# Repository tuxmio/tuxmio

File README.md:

## Hi there 👋
This project was started to combine industrial controllers, open-source controllers, and the freedom of customization.

1. Project Name & Description
   
    TUXMIO= 2XMIO=MIO+MIO=Make It Own Modular Input/Output System
TUXMIO is a customizable Modular Input/Output System. It allows users to mix and match hardware while keeping full control over their automation systems.

2. Features
   
    ✔ Modular Design – Easily expand and customize I/O modules based on project needs.
  
    ✔ Hybrid Compatibility – Works with both industrial controllers (PLC, DCS) and open-source hardware (Arduino, ESP32, Raspberry Pi).
  
    ✔ Cross-Platform Support – Works with Linux, Windows, and embedded systems.
  
    ✔ Industrial-Grade Reliability – Designed for rugged environments with robust protection features.
  
    ✔ Flexible Manufacturing Options – Users can build it themselves, order custom production, or buy pre-assembled modules.

3. Installation & Setup
   
    Hardware:
  
    ✔ Choose your favorite open-source controller
  
    ✔ Connect it to TUXMIO
  
    ✔ Enjoy your controller in an industrial environment
  
    Software & Setup:
  
    Use your usual tools for firmware installation, configuration, and testing—just like you always do!

4. Usage

    After setup, just start your system and enjoy your creation.

5. Hardware Requirements

    ✔ Choose your favorite open-source controller (Arduino, Raspberry Pi, ESP32, etc.).
   
    ✔ TUXMIO modules (customize based on your needs).
   
    ✔ You can prepare your own power supply voltages, or use the TUXMIO PS board for convenience.
   
    ✔ Any additional sensors, actuators, or peripherals based on your project.

6. Contributing

    Hey, I’m not a professional in electronics, 3D design, or prototyping, so please be understanding and forgiving if you spot any mistakes or discrepancies. 😊
   
    If you’d like to help out, here’s how you can contribute:
   
      ✔ Fork the Repo: Feel free to fork this repo and create a branch with your changes.
   
      ✔ Submit a Pull Request: When you're ready, send over a pull request!
   
      ✔ Report Issues: If you notice any bugs or have suggestions, don’t hesitate to open an issue.
   
      ✔ Join the Fun: Let’s work together to make this project better and take it to new heights!

7. License
   TUXMIO is proudly open in both mind and design.
All software and firmware are shared under the MIT License — free to use, modify, and remix however you like.
All hardware designs (schematics, PCBs, 3D models) follow the CERN Open Hardware License – Permissive v2.0, allowing you to build, improve, and even sell your own versions, as long as you keep the original attribution intact! 😊

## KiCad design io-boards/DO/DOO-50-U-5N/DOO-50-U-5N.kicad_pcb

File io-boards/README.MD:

┌──────┬────────────┬───────────┬─────────────────────────────────────────────┬───────────────────────────────────────────────────────────────────────────────┐
│ Code │ Complexity │ Priority  │ Description                                 │ Notes                                                                         │
├──────┼────────────┼───────────┼─────────────────────────────────────────────┼───────────────────────────────────────────────────────────────────────────────┤
│ DI   │ 0          │ 1         │ Direct digital input (NPN/PNP stabilized)   │ Simple design, direct to MCU or buffer input.                                 │
│ DI   │ 4          │ -         │ Differential digital input (super-fast OC)  │ High-speed differential inputs, open-collector tolerant.                      │
│ DI   │ 2          │ -         │ Optocoupled digital input (NPN/PNP)         │ Isolated voltage sensing, moderate complexity.                                │
│ DO   │ 0          │ 1         │ Direct digital output (NPN/PNP stabilized)  │ Transistor-based output, low-side/high-side variants possible.                │
│ DO   │ 2          │ -         │ Optocoupled digital output (short-prot.)    │ Protected, diagnostic LEDs, block on short.                                   │
│ DO   │ 4          │ -         │ Super-fast optocoupled digital output       │ High-speed driver, isolation + diagnostics.                                   │
│ DO   │ 4          │ -         │ Differential digital output (OC)            │ Fast differential output, open-collector style.                               │
│ DO   │ 1          │ 2         │ Relay output                                │ Mechanical relay, user-changeable type.                                       │
│ DO   │ 1          │ 2         │ SSR relay output                            │ Solid State Relay variant.                                                    │
│ AI   │ 0          │ 1         │ Direct analog input 0–5V                    │ Basic ADC interface.                                                          │
│ AI   │ 1          │ -         │ 0–10V analog input                          │ Most common industrial input range.                                           │
│ AI   │ 2          │ -         │ ±10V analog input                           │ Bipolar measurement range.                                                    │
│ AI   │ 4          │ 5         │ 0–5mA analog input                          │ Requires precise current sensing, maybe external supply.                      │
│ AI   │ 4          │ 5         │ 0–20mA analog input                         │ Current loop sensing, possibly needs shunt resistor.                          │
│ AI   │ 4          │ 5         │ Low-voltage 0–10mV analog input             │ For small-signal sensors, instrumentation amp required.                       │
│ AI   │ 3          │ 5         │ Thermocouple input                          │ Requires CJC, precision ADC, low noise.                                       │
│ AI   │ 3          │ 5         │ RTD input (PT100/PT1000)                    │ Requires excitation and bridge measurement.                                   │
│ AO   │ 0          │ 1         │ Direct analog output 0–5V                   │ Simple DAC output.                                                            │
│ AO   │ 2          │ 2         │ 0–10V analog output                         │ Standard industrial output range.                                             │
│ AO   │ 2          │ 5         │ ±10V analog output                          │ Bipolar DAC driver, requires dual supply.                                     │
│ AO   │ 4          │ 3         │ 0–20mA analog output                        │ Current loop output, supply-dependent.                                        │
└──────┴────────────┴───────────┴─────────────────────────────────────────────┴───────────────────────────────────────────────────────────────────────────────┘

Enhanced I/O Function Table with ABC Codes
#	Old Code	New Code	Description	Notes / Feature keywords
1	DI	DID	Direct Digital Input (NPN/PNP stabilized)	simplest form, direct connection
2	DI	DIF	Differential Digital Input (superfast OC)	high-speed, open-collector compatible
3	DI	DIO	Optocoupled Digital Input (NPN/PNP voltage)	isolated, standard industrial input
4	DO	DOD	Direct Digital Output (NPN/PNP stabilized)	simple transistor output
5	DO	DOO	Optocoupled Digital Output (short-prot, diag)	isolated, protected, LED indicators
6	DO	DOF	Fast Optocoupled Digital Output (superfast)	high-speed variant
7	DO	DOH	Differential (High-speed OC) Digital Output	OC differential drivers
8	DO	DOR	Relay Output (mechanical relays)	changeable relay sockets
9	DO	DOS	SSR Output (Solid-State Relay)	solid-state version
10	AI	AIV	Analog Voltage Input (0–5V, 0–10V, ±10V)	voltage-based measurement
11	AI	AIC	Analog Current Input (0–5mA, 0–20mA)	current loop or shunt measurement
12	AI	AIL	Low-Voltage / Millivolt Input	instrumentation, low-noise sensors
13	AI	AIT	Thermocouple Input	temperature, requires CJC
14	AI	AIR	Resistance / RTD Input (PT100/PT1000)	with excitation and linearization
15	AO	AOV	Analog Voltage Output (0–5V, 0–10V, ±10V)	DAC-based voltage output
16	AO	AOC	Analog Current Output (0–20mA)	current loop output
17	COM	CCI	Communication Interface Input (e.g., RS, CAN)	receives data
18	COM	CCO	Communication Interface Output	transmits data
19	COM	CCX	Communication Transceiver / Bidirectional	bidirectional (e.g., RS485, CAN, I²C)

1st letter: Domain
D → Digital
A → Analog
C → Communication

2nd letter: Direction
I → Input
O → Output
X → Bidirectional / mixed

3rd letter: Feature

D = Direct
O = Optocoupled
F = Fast / Differential
R = Relay
S = Solid State
V = Voltage
C = Current
L = Low voltage / millivolt
T = Thermocouple
R = RTD (resistance sensor)
H = High-speed / OC
X = Mixed / special

┌────────────┬───────────┬───────────────────────────────────────────────┐
│ Letter Pos │ Represents│ Example Letters / Meaning                     │
├────────────┼───────────┼───────────────────────────────────────────────┤
│ 1st        │ Domain    │ D = Digital, A = Analog, C = Communication    │
│ 2nd        │ Direction │ I = Input, O = Output, X = Bidirectional      │
│ 3rd        │ Feature   │ D = Direct, O = Optocoupled, F = Fast,        │
│            │           │ R = Relay, S = Solid-state, V = Voltage,      │
│            │           │ C = Current, L = Low-voltage, T = TC, R = RTD │
└────────────┴───────────┴───────────────────────────────────────────────┘

<ABC>-<LS>-<PT>-<RPO>-Vx.xx

where:
ABC = 3-letter functional code = [Domain][Direction][Feature]
    Domain: A = Analog, D = Digital (use “Digital”), C = Communication
    Direction: I = Input, O = Output, X = Bidirectional
    Feature: domain-specific (e.g. D=Direct, O=Optocoupled, F=Fast/Differential, R=Relay, S=SolidState, V=Voltage, C=Current, L=Low-voltage, T=Thermocouple, R=RTD, H=High-speed, X=Mixed)
LS = two digits: [LogicLevel][SocketType]
    LogicLevel (first digit): 3 = 3.3 V logic, 5 = 5 V logic, 9 = Mixed/Auto/Dual
    SocketType (second digit): 0 = Socket A, 1 = Socket B, 2 = Socket C, 3 = Socket D
PT = Peripheral Type (single letter)
    U = Voltage-type peripheral
    C = Current-type peripheral
RPO = Range code + Peripheral Option (two chars)
Range code (digit): Voltage codes (for U)
    0 = sink-mode NPN (logic sink)
    1 = 3.3/5 V logic-level field
    2 = 10 V
    3 = 12 V
    4 = 15 V
    5 = 24 V
    6 = 230 VAC
Range code (digit): Current codes (for C)
    0 = 0–5 mA
    1 = 0–20 mA
    2 = 4–20 mA
    3 = −20 mA … +20 mA
Peripheral Option (letter, immediately after range digit):
    N = Sink mode (NPN)
    P = Source mode (PNP)
    B = Bipolar
Vx.xx = Version (major.minor) e.g. V0.01

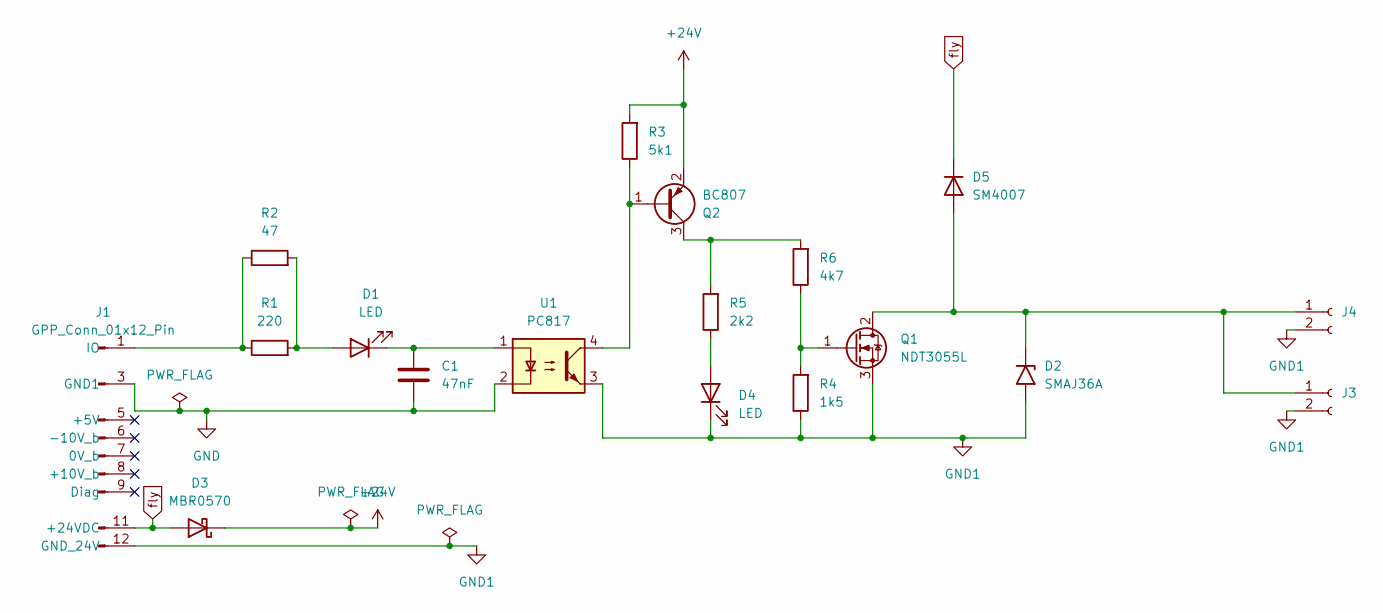
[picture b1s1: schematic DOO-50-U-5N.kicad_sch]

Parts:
C1: 47nF; C_0201_0603Metric
D1, D4: LED; LED_0402_1005Metric_Pad0.77x0.64mm_HandSolder
D2: SMAJ36A; D_SMA
D3: MBR0570; D_SOD-123
D5: SM4007; D_MELF_Handsoldering
J1: GPP_Conn_01x12_Pin; IO_GPP_PinHeader_1x12_P2.54mm_Horizontal
J3: Conn_01x02_Socket; KF141x_SMD
J4: Conn_01x02_Socket; PinSocket_1x02_P2.54mm_Horizontal
Q1: NDT3055L; SOT-223-3_TabPin2
Q2: BC807; SOT-23
R1: 220; R_0402_1005Metric_Pad0.72x0.64mm_HandSolder
R2: 47; R_0402_1005Metric_Pad0.72x0.64mm_HandSolder
R3: 5k1; R_0402_1005Metric_Pad0.72x0.64mm_HandSolder
R4: 1k5; R_0402_1005Metric_Pad0.72x0.64mm_HandSolder
R5: 2k2; R_0402_1005Metric_Pad0.72x0.64mm_HandSolder
R6: 4k7; R_0402_1005Metric_Pad0.72x0.64mm_HandSolder
U1: PC817; DIP-4_W7.62mm_SMDSocket_SmallPads

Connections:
+24V: D3.1 (K), Q2.2 (E), R3.2
GND: C1.2, J1.3 (GND1), U1.2
GND1: D2.2 (A2), D4.1 (K), J1.12 (GND_24V), J3.2, J4.2, Q1.3 (S), R4.1, U1.3
unnamed: D1.2 (A), R1.2, R2.2
unnamed: C1.1, D1.1 (K), U1.1
unnamed: D2.1 (A1), D5.2 (A), J3.1, J4.1, Q1.2 (D)
unnamed: D4.2 (A), R5.1
unnamed: J1.1 (IO), R1.1, R2.1
unnamed: Q1.1 (G), R4.2, R6.1
unnamed: Q2.1 (B), R3.1, U1.4
unnamed: Q2.3 (C), R5.2, R6.2
fly: D3.2 (A), D5.1 (K), J1.11 (+24VDC)

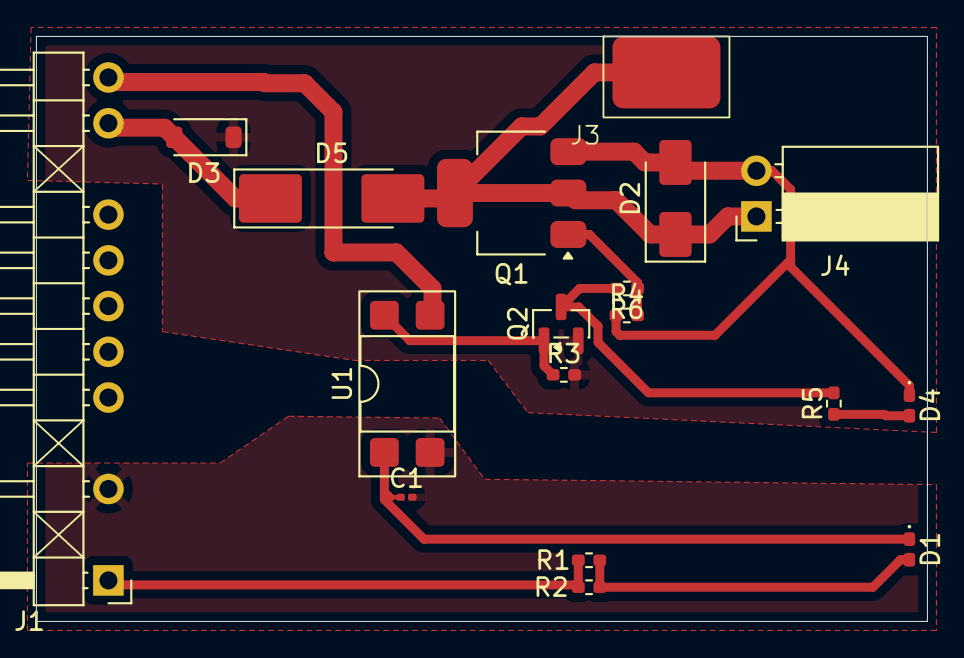
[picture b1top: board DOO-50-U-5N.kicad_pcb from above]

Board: 2 copper layers, 49.5 x 32.5 mm, 18 parts (0 on the bottom side), 12 nets.

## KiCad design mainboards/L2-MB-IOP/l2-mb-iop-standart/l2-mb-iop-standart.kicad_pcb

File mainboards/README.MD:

TUXMIO Mainboard Classification
┌──────────────┬──────────────────────────────┬────────┬──────────────────────────────────────────────────────────────────────────────┐
│ Directory    │ Full Name                    │ Level  │ Description                                                                  │
├──────────────┼──────────────────────────────┼────────┼──────────────────────────────────────────────────────────────────────────────┤
│ L0-MB-PML    │ Power Management Layer       │ L0     │ Handles power entry, conversion, and protection (fuse, surge, polarity).     │
│              │                              │        │ Supplies regulated voltages to upper layers.                                 │
├──────────────┼──────────────────────────────┼────────┼──────────────────────────────────────────────────────────────────────────────┤
│ L1-MB-CIM    │ Controller Interface Module  │ L1     │ Hosts the main controller (MCU, SBC, or SoM). Manages logic, communication   │
│              │                              │        │ and links between the power and I/O layers.                                  │
├──────────────┼──────────────────────────────┼────────┼──────────────────────────────────────────────────────────────────────────────┤
│ L2-MB-IOP    │ Input/Output Peripherals     │ L2     │ Provides interface for I/O boards, sensors, and actuators. Includes sockets  │
│              │                              │        │ for I/O boards. each socket only supports specific I/O board types           │
└──────────────┴──────────────────────────────┴────────┴──────────────────────────────────────────────────────────────────────────────┘
 
   ┌┐   ┌┐   ┌┐   ┌┐   ┌┐   ┌┐   ┌┐   
   ||   ||   ||   ||   ||   ||   ||
   ||   ||   ||   ||   ||   ||   ||  ← I/O Boards
   ||   ||   ||   ||   ||   ||   ||
   └┘   └┘   └┘   └┘   └┘   └┘   └┘   
   ┌──────────────────────────────┐
   │  L2 – MB-IOP  (Peripherals)  │  ← I/O Expansion Layer
   └─────────────┬────────────────┘
                 │
   ┌─────────────┴────────────────┐
   │  L1 – MB-CIM  (Controller)   │  ← Processing & Communication Layer
   └─────────────┬────────────────┘
                 │
   ┌─────────────┴────────────────┐
   │  L0 – MB-PML  (Power)        │  ← Power & Protection Base Layer
   └──────────────────────────────┘

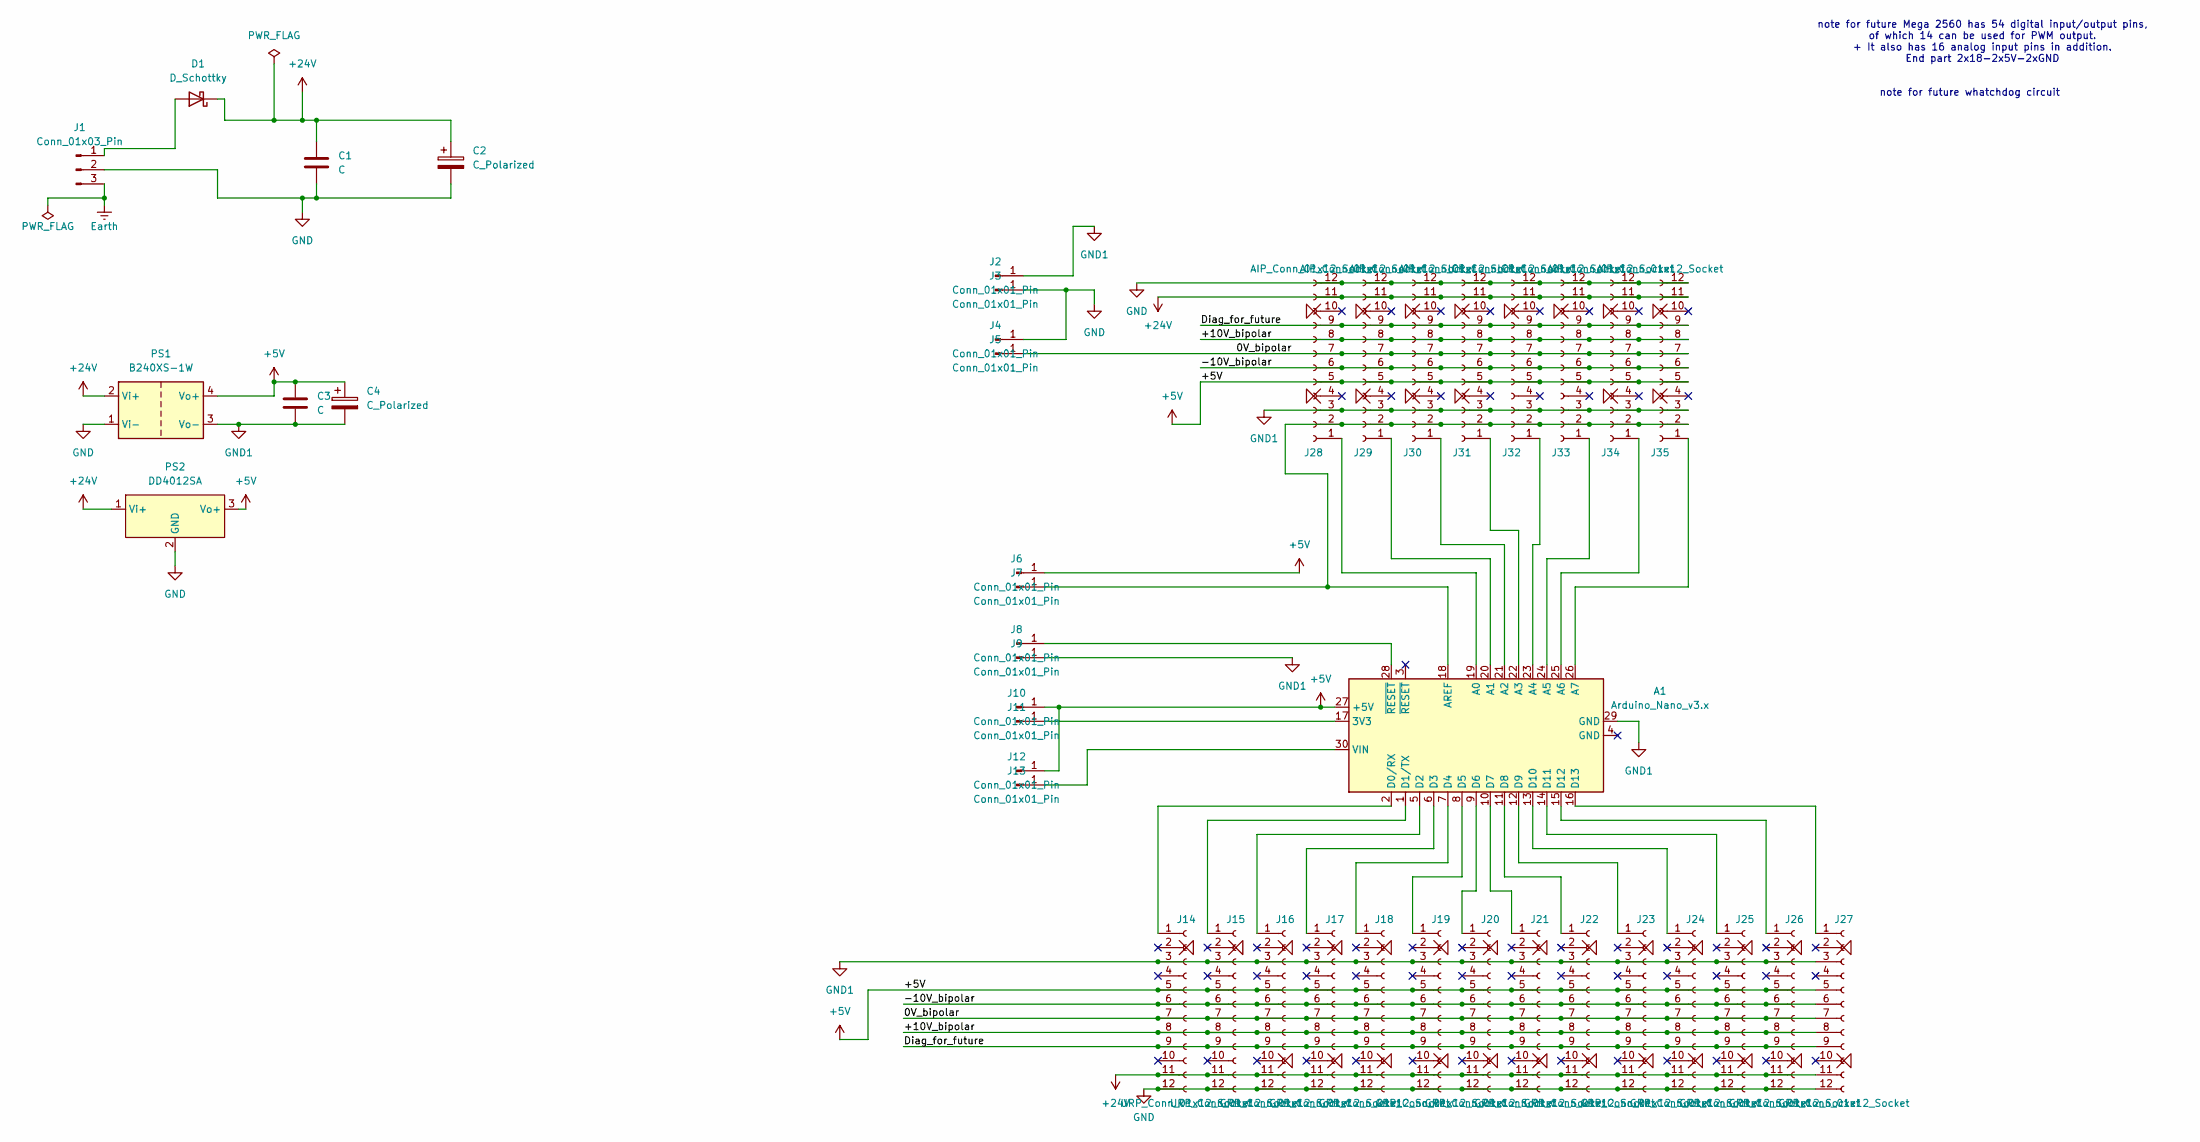
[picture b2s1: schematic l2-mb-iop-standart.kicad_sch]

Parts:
A1: Arduino_Nano_v3.x; Arduino_Nano
C1, C3: C
C2, C4: C_Polarized
D1: D_Schottky
J1: Conn_01x03_Pin
J2, J3, J4, J5, J6, J7, J8, J9, J10, J11, J12, J13: Conn_01x01_Pin
J14, J15: URP_Conn_01x12_Socket; MB_URP_PinSocket_1x12_P2.54mm_Vertical
J16, J17, J18, J19, J20, J21, J22, J23, J24, J25, J26, J27: GPP_Conn_01x12_Socket; MB_GPP_PinSocket_1x12_P2.54mm_Vertical
J28, J29, J30, J31, J34, J35: AIP_Conn_01x12_Socket; MB_AIP_PinSocket_1x12_P2.54mm_Vertical
J32, J33: ICP_Conn_01x12_Socket; MB_ICP_PinSocket_1x12_P2.54mm_Vertical
PS1: B240XS-1W
PS2: DD4012SA

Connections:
+5V: A1.27 (+5V), C3.1, C4.1, J6.1, J10.1, J12.1, J14.5 (Diag), J15.5 (Diag), J16.5 (Diag), J17.5 (Diag), J18.5 (Diag), J19.5 (Diag), J20.5 (Diag), J21.5 (Diag), J22.5 (Diag), J23.5 (Diag), J24.5 (Diag), J25.5 (Diag), J26.5 (Diag), J27.5 (Diag), J28.5 (Diag), J29.5 (Diag), J30.5 (Diag), J31.5 (Diag), J32.5 (Diag), J33.5 (Diag), J34.5 (Diag), J35.5 (Diag), PS1.4 (Vo+), PS2.3 (Vo+)
+24V: C1.1, C2.1, D1.1 (K), J14.11 (+24VDC), J15.11 (+24VDC), J16.11 (+24VDC), J17.11 (+24VDC), J18.11 (+24VDC), J19.11 (+24VDC), J20.11 (+24VDC), J21.11 (+24VDC), J22.11 (+24VDC), J23.11 (+24VDC), J24.11 (+24VDC), J25.11 (+24VDC), J26.11 (+24VDC), J27.11 (+24VDC), J28.11 (+24VDC), J29.11 (+24VDC), J30.11 (+24VDC), J31.11 (+24VDC), J32.11 (+24VDC), J33.11 (+24VDC), J34.11 (+24VDC), J35.11 (+24VDC), PS1.2 (Vi+), PS2.1 (Vi+)
/0V_bipolar: J5.1, J14.7 (0V_b), J15.7 (0V_b), J16.7 (0V_b), J17.7 (0V_b), J18.7 (0V_b), J19.7 (0V_b), J20.7 (0V_b), J21.7 (0V_b), J22.7 (0V_b), J23.7 (0V_b), J24.7 (0V_b), J25.7 (0V_b), J26.7 (0V_b), J27.7 (0V_b), J28.7 (0V_b), J29.7 (0V_b), J30.7 (0V_b), J31.7 (0V_b), J32.7 (0V_b), J33.7 (0V_b), J34.7 (0V_b), J35.7 (0V_b)
/+10V_bipolar: J14.8 (+10V_b), J15.8 (+10V_b), J16.8 (+10V_b), J17.8 (+10V_b), J18.8 (+10V_b), J19.8 (+10V_b), J20.8 (+10V_b), J21.8 (+10V_b), J22.8 (+10V_b), J23.8 (+10V_b), J24.8 (+10V_b), J25.8 (+10V_b), J26.8 (+10V_b), J27.8 (+10V_b), J28.8 (+10V_b), J29.8 (+10V_b), J30.8 (+10V_b), J31.8 (+10V_b), J32.8 (+10V_b), J33.8 (+10V_b), J34.8 (+10V_b), J35.8 (+10V_b)
/-10V_bipolar: J14.6 (-10V_b), J15.6 (-10V_b), J16.6 (-10V_b), J17.6 (-10V_b), J18.6 (-10V_b), J19.6 (-10V_b), J20.6 (-10V_b), J21.6 (-10V_b), J22.6 (-10V_b), J23.6 (-10V_b), J24.6 (-10V_b), J25.6 (-10V_b), J26.6 (-10V_b), J27.6 (-10V_b), J28.6 (-10V_b), J29.6 (-10V_b), J30.6 (-10V_b), J31.6 (-10V_b), J32.6 (-10V_b), J33.6 (-10V_b), J34.6 (-10V_b), J35.6 (-10V_b)
/Diag_for_future: J14.9 (N/A_Pin_9), J15.9 (N/A_Pin_9), J16.9 (N/A_Pin_9), J17.9 (N/A_Pin_9), J18.9 (N/A_Pin_9), J19.9 (N/A_Pin_9), J20.9 (N/A_Pin_9), J21.9 (N/A_Pin_9), J22.9 (N/A_Pin_9), J23.9 (N/A_Pin_9), J24.9 (N/A_Pin_9), J25.9 (N/A_Pin_9), J26.9 (N/A_Pin_9), J27.9 (N/A_Pin_9), J28.9 (N/A_Pin_9), J29.9 (N/A_Pin_9), J30.9 (N/A_Pin_9), J31.9 (N/A_Pin_9), J32.9 (N/A_Pin_9), J33.9 (N/A_Pin_9), J34.9 (N/A_Pin_9), J35.9 (N/A_Pin_9)
Earth: J1.3
GND: C1.2, C2.2, J1.2, J3.1, J4.1, J14.12 (GND_24V), J15.12 (GND_24V), J16.12 (GND_24V), J17.12 (GND_24V), J18.12 (GND_24V), J19.12 (GND_24V), J20.12 (GND_24V), J21.12 (GND_24V), J22.12 (GND_24V), J23.12 (GND_24V), J24.12 (GND_24V), J25.12 (GND_24V), J26.12 (GND_24V), J27.12 (GND_24V), J28.12 (GND_24V), J29.12 (GND_24V), J30.12 (GND_24V), J31.12 (GND_24V), J32.12 (GND_24V), J33.12 (GND_24V), J34.12 (GND_24V), J35.12 (GND_24V), PS1.1 (Vi-), PS2.2 (GND)
GND1: A1.29 (GND), C3.2, C4.2, J2.1, J9.1, J14.3 (GND1), J15.3 (GND1), J16.3 (GND1), J17.3 (GND1), J18.3 (GND1), J19.3 (GND1), J20.3 (GND1), J21.3 (GND1), J22.3 (GND1), J23.3 (GND1), J24.3 (GND1), J25.3 (GND1), J26.3 (GND1), J27.3 (GND1), J28.3 (GND1), J29.3 (GND1), J30.3 (GND1), J31.3 (GND1), J32.3 (GND1), J33.3 (GND1), J34.3 (GND1), J35.3 (GND1), PS1.3 (Vo-)
unnamed: A1.17 (3V3), J11.1
unnamed: A1.19 (A0), J28.1 (IO)
unnamed: A1.20 (A1), J29.1 (IO)
unnamed: A1.21 (A2), J30.1 (IO)
unnamed: A1.22 (A3), J31.1 (IO)
unnamed: A1.23 (A4), J32.1 (IO)
unnamed: A1.24 (A5), J33.1 (IO)
unnamed: A1.25 (A6), J34.1 (IO)
unnamed: A1.26 (A7), J35.1 (IO)
unnamed: A1.18 (AREF), J7.1, J28.2 (A_Ref), J29.2 (A_Ref), J30.2 (A_Ref), J31.2 (A_Ref), J32.2 (A_Ref), J33.2 (A_Ref), J34.2 (A_Ref), J35.2 (A_Ref)
unnamed: A1.2 (D0/RX), J14.1 (IO)
unnamed: A1.1 (D1/TX), J15.1 (IO)
unnamed: A1.5 (D2), J16.1 (IO)
unnamed: A1.6 (D3), J17.1 (IO)
unnamed: A1.7 (D4), J18.1 (IO)
unnamed: A1.8 (D5), J19.1 (IO)
unnamed: A1.9 (D6), J20.1 (IO)
unnamed: A1.10 (D7), J21.1 (IO)
unnamed: A1.11 (D8), J22.1 (IO)
unnamed: A1.12 (D9), J23.1 (IO)
unnamed: A1.13 (D10), J24.1 (IO)
unnamed: A1.14 (D11), J25.1 (IO)
unnamed: A1.15 (D12), J26.1 (IO)
unnamed: A1.16 (D13), J27.1 (IO)
unnamed: A1.30 (VIN), J13.1
unnamed: D1.2 (A), J1.1
unnamed: A1.28 (~RESET), J8.1

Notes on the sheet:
note for future Mega 2560 has 54 digital input/output pins, of which 14 can be used for PWM output. + It also has 16 analog input pins in addition. End part 2x18-2x5V-2xGND
note for future whatchdog circuit

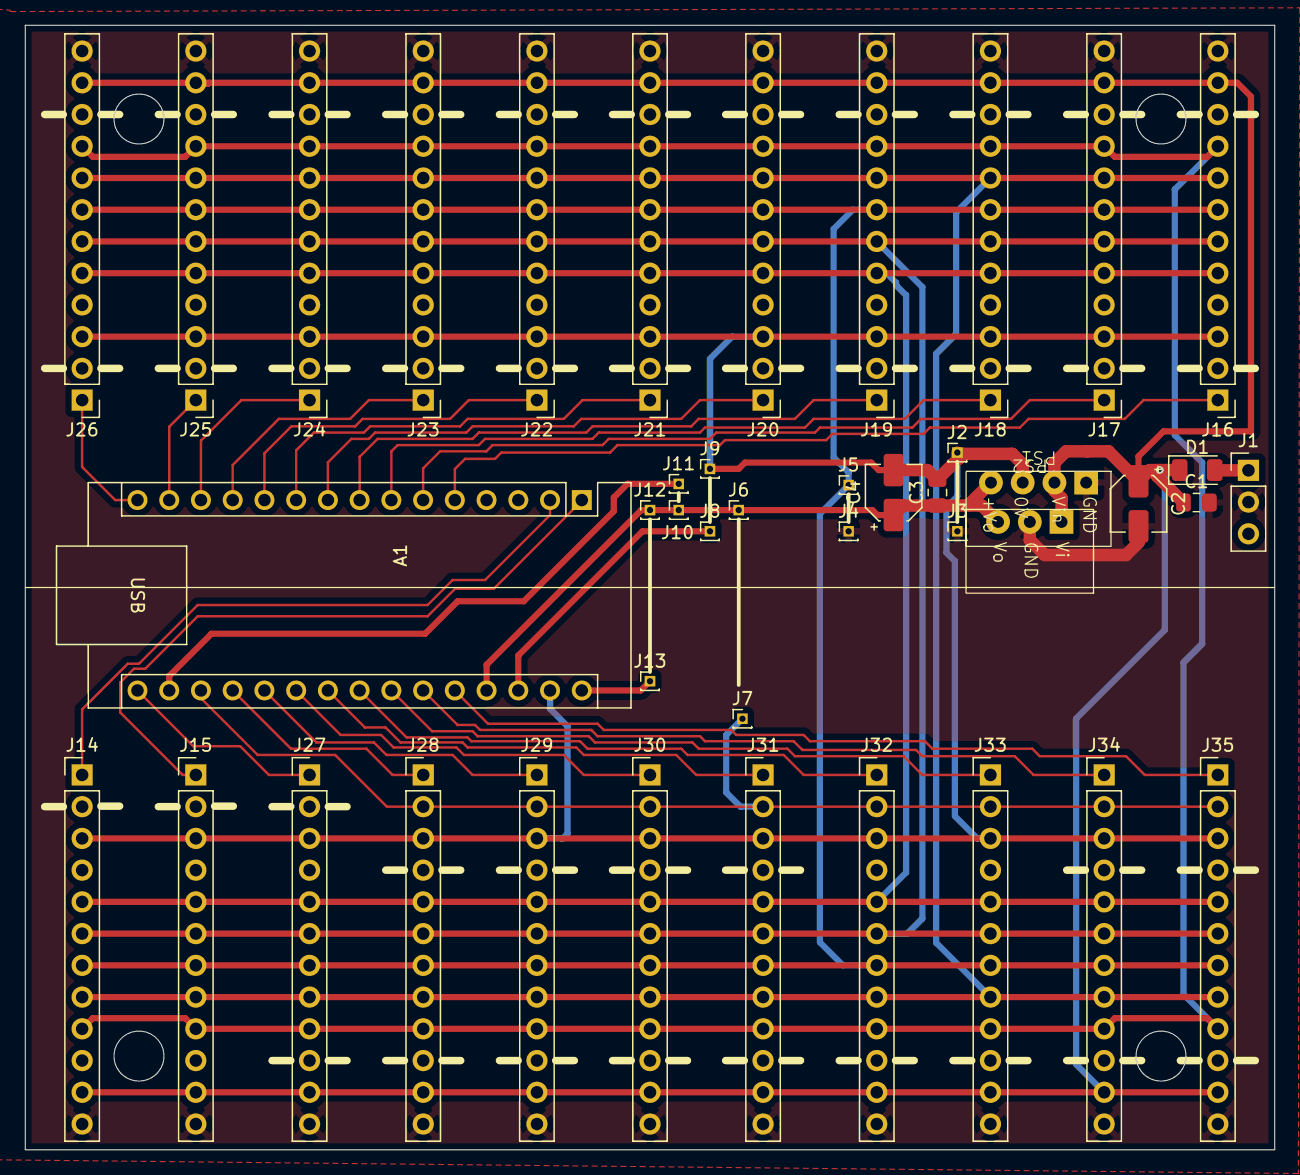
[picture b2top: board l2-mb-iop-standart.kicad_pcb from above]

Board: 2 copper layers, 100.0 x 90.0 mm, 43 parts (0 on the bottom side), 35 nets.

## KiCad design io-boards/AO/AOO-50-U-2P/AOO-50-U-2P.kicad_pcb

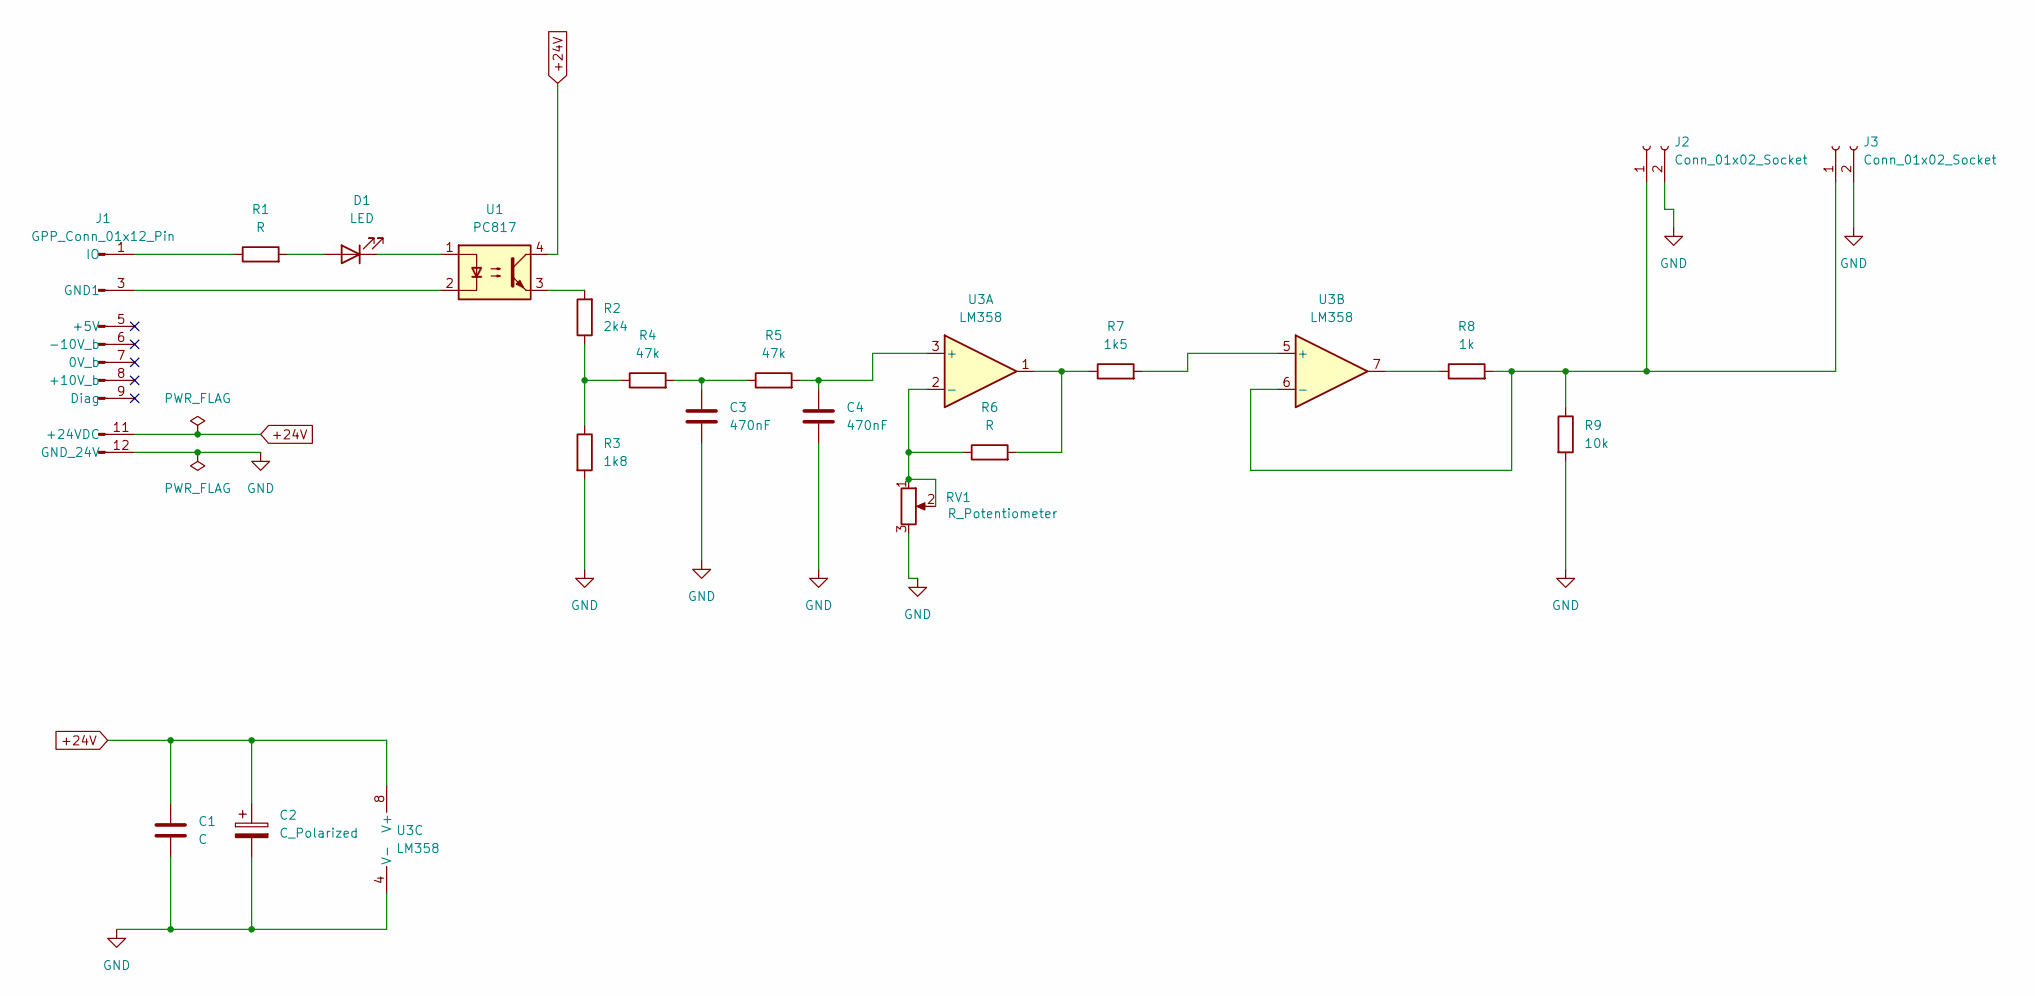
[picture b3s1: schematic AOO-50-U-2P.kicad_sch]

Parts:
C1: C; C_Disc_D4.7mm_W2.5mm_P5.00mm
C2: C_Polarized; CP_Radial_D4.0mm_P2.00mm
C3, C4: 470nF; C_Disc_D6.0mm_W2.5mm_P5.00mm
D1: LED; LED_D3.0mm
J1: GPP_Conn_01x12_Pin; IO_GPP_PinHeader_1x12_P2.54mm_Horizontal
J2: Conn_01x02_Socket; KF141x_SMD
J3: Conn_01x02_Socket; PinSocket_1x02_P2.54mm_Horizontal
R1, R6: R; R_Axial_DIN0204_L3.6mm_D1.6mm_P5.08mm_Horizontal
R2: 2k4; R_Axial_DIN0204_L3.6mm_D1.6mm_P5.08mm_Horizontal
R3: 1k8; R_Axial_DIN0204_L3.6mm_D1.6mm_P5.08mm_Horizontal
R4, R5: 47k; R_Axial_DIN0204_L3.6mm_D1.6mm_P5.08mm_Horizontal
R7: 1k5; R_Axial_DIN0204_L3.6mm_D1.6mm_P5.08mm_Horizontal
R8: 1k; R_Axial_DIN0204_L3.6mm_D1.6mm_P5.08mm_Horizontal
R9: 10k; R_Axial_DIN0204_L3.6mm_D1.6mm_P5.08mm_Horizontal
RV1: R_Potentiometer; Potentiometer_Vishay_148-149_Single_Vertical
U1: PC817; DIP-4_W7.62mm_SMDSocket_SmallPads
U3: LM358; DIP-8_W7.62mm

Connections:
+24V: C1.1, C2.1, J1.11 (+24VDC), U1.4, U3.8 (V+)
GND: C1.2, C2.2, C3.2, C4.2, J1.12 (GND_24V), J2.2, J3.2, R3.2, R9.2, RV1.3, U3.4 (V-)
unnamed: C3.1, R4.2, R5.1
unnamed: D1.2 (A), R1.2
unnamed: D1.1 (K), U1.1
unnamed: J1.3 (GND1), U1.2
unnamed: J1.1 (IO), R1.1
unnamed: J2.1, J3.1, R8.2, R9.1, U3.6 (-)
unnamed: R2.1, R3.1, R4.1
unnamed: R2.2, U1.3
unnamed: R6.2, R7.1, U3.1
unnamed: R8.1, U3.7
unnamed: C4.1, R5.2, U3.3 (+)
unnamed: R6.1, RV1.1, RV1.2, U3.2 (-)
unnamed: R7.2, U3.5 (+)

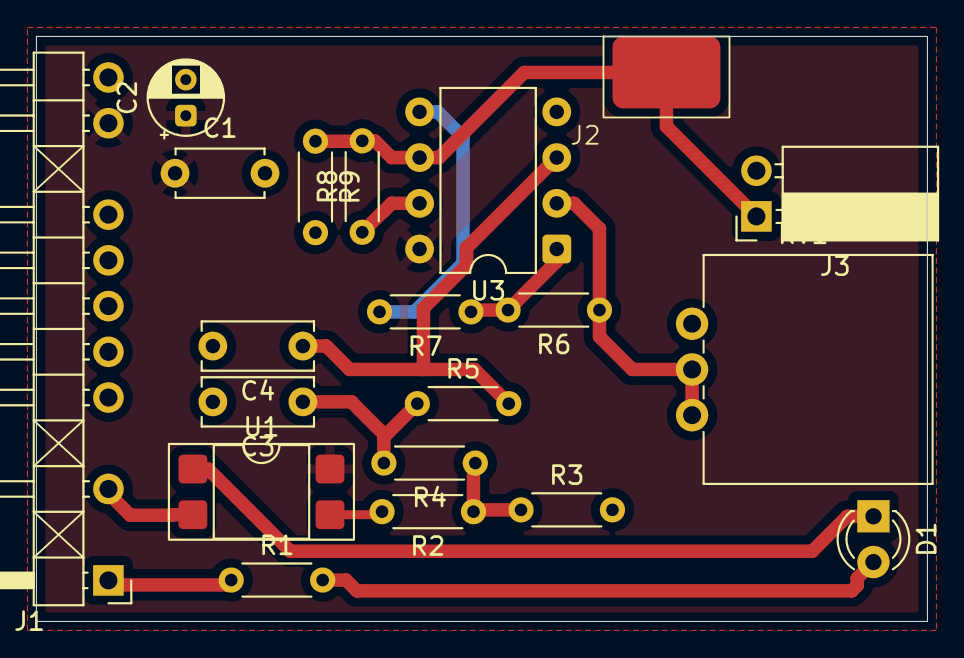
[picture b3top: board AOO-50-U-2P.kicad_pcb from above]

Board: 2 copper layers, 49.5 x 32.5 mm, 20 parts (0 on the bottom side), 15 nets.

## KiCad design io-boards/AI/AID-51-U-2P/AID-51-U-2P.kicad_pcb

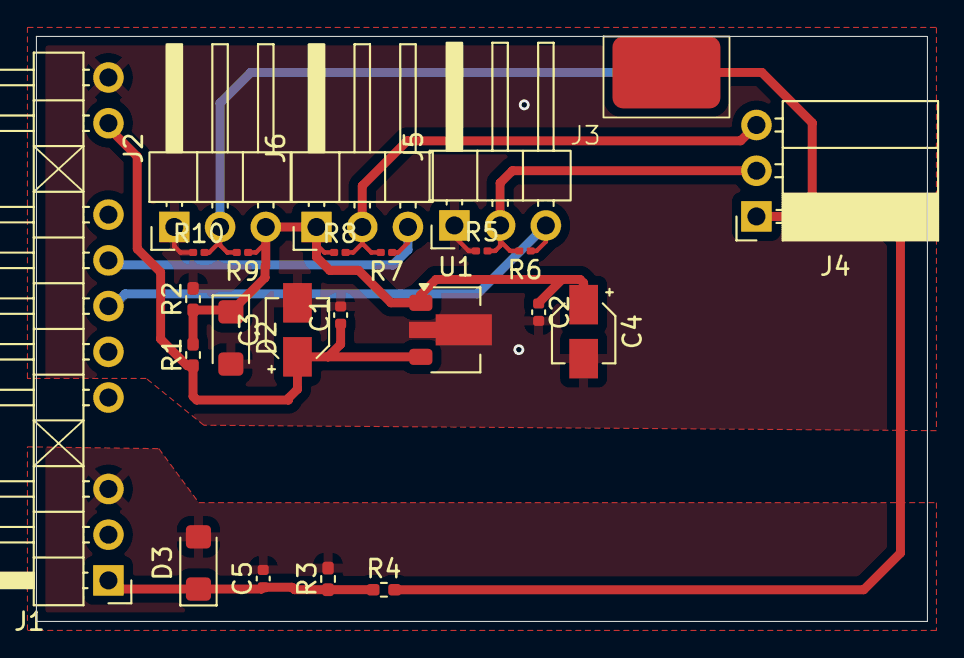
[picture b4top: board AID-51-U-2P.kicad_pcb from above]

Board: 2 copper layers, 49.5 x 32.5 mm, 24 parts (0 on the bottom side), 11 nets.

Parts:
C1, C2: 100nF; C_0402_1005Metric
C3: 10uf 50V; CP_Elec_3x5.3
C4: 10uF 50V; CP_Elec_3x5.3
C5: 10nF; C_0402_1005Metric
D2: 11V - BZD27C11P; D_SMF
D3: 5V1 - BZD27C5V1P; D_SMF
J1: AIP_Conn_01x12_Pin; IO_AIP_PinHeader_1x12_P2.54mm_Horizontal
J2, J5, J6: Conn_01x03_Pin; PinHeader_1x03_P2.54mm_Horizontal
J3: Conn_01x02_Socket; KF141x_SMD
J4: Conn_01x03_Socket; PinSocket_1x03_P2.54mm_Horizontal
R1: 2k2; R_0402_1005Metric_Pad0.72x0.64mm_HandSolder
R2: 1k8; R_0402_1005Metric_Pad0.72x0.64mm_HandSolder
R3, R4: 5k1; R_0402_1005Metric_Pad0.72x0.64mm_HandSolder
R5, R6, R7, R8, R9, R10: j; R_0201_0603Metric
U1: L78L10_SOT89; SOT-89-3

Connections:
GND: C1.2, C2.2, C3.2, C4.2, D2.2 (A), J1.12 (GND_24V), J2.1, J5.1, R2.2, R5.1, R10.1, U1.2 (GND)
GND1: C5.2, D3.2 (A), J1.3 (GND1), R3.2
unnamed: C2.1, C4.1, D2.1 (K), J2.3, J6.1, R1.2, R2.1, R8.1, R9.1, U1.1 (OUT)
unnamed: C5.1, D3.1 (K), J1.1 (IO), R3.1, R4.1
unnamed: J1.7 (0V_b), J5.3, R6.1
unnamed: J1.8 (+10V_b), J6.3, R7.1
unnamed: C1.1, C3.1, J1.11 (+24VDC), R1.1, U1.3 (IN)
unnamed: J2.2, J3.2, R9.2, R10.2
unnamed: J3.1, J4.1, R4.2
unnamed: J4.2, J5.2, R5.2, R6.2
unnamed: J4.3, J6.2, R7.2, R8.2

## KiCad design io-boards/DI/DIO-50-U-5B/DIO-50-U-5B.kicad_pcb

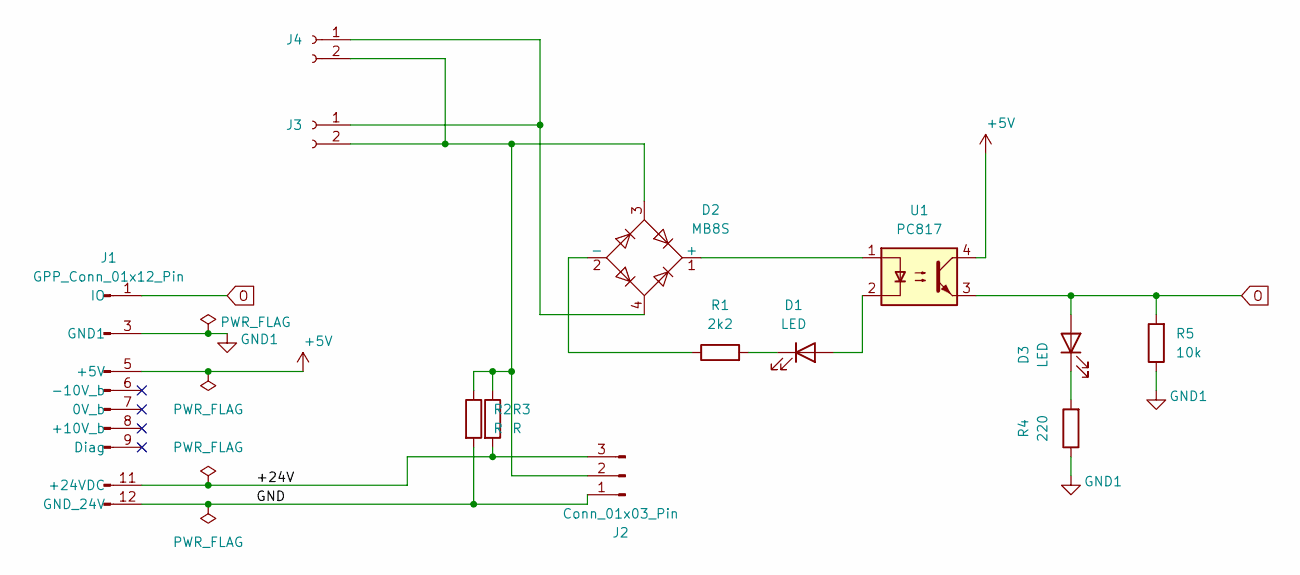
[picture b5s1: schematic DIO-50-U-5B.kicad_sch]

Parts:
D1, D3: LED; LED_0402_1005Metric_Pad0.77x0.64mm_HandSolder
D2: MB8S; OnSemi_751EP_SOIC-4_3.9x4.725mm_P2.54mm
J1: GPP_Conn_01x12_Pin; IO_GPP_PinHeader_1x12_P2.54mm_Horizontal
J2: Conn_01x03_Pin; PinHeader_1x03_P2.54mm_Horizontal
J3: Conn_01x02_Socket; KF141x_SMD
J4: Conn_01x02_Socket; PinSocket_1x02_P2.54mm_Horizontal
R1: 2k2; R_0402_1005Metric_Pad0.72x0.64mm_HandSolder
R2, R3: R; R_0201_0603Metric_Pad0.64x0.40mm_HandSolder
R4: 220; R_0402_1005Metric_Pad0.72x0.64mm_HandSolder
R5: 10k; R_0402_1005Metric_Pad0.72x0.64mm_HandSolder
U1: PC817; DIP-4_W7.62mm_SMDSocket_SmallPads

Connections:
+5V: J1.5 (+5V), U1.4
/+24V: J1.11 (+24VDC), J2.3, R3.2
/GND: J1.12 (GND_24V), J2.1, R2.2
GND1: J1.3 (GND1), R4.1, R5.1
unnamed: D1.2 (A), U1.2
unnamed: D1.1 (K), R1.2
unnamed: D2.1 (+), U1.1
unnamed: D2.2 (-), R1.1
unnamed: D3.1 (K), R4.2
unnamed: D2.3, J2.2, J3.2, J4.2, R2.1, R3.1
unnamed: D2.4, J3.1, J4.1
O: D3.2 (A), J1.1 (IO), R5.2, U1.3

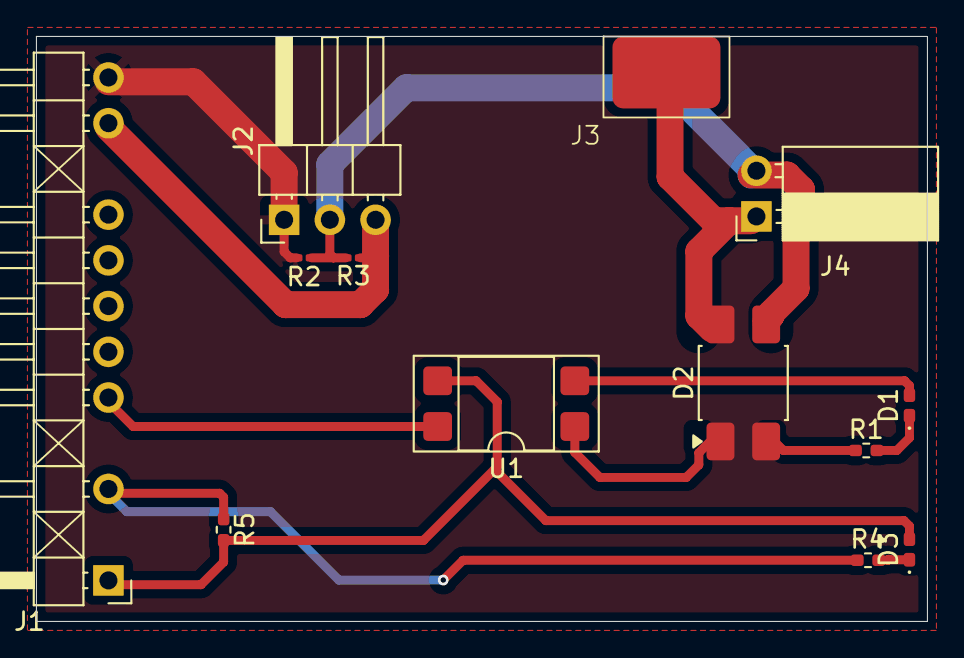
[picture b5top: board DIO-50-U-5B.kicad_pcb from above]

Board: 2 copper layers, 49.5 x 32.5 mm, 13 parts (0 on the bottom side), 12 nets.

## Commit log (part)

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2025-10-10 ZeroStone of Tuxmio project
2025-10-10 Structure added
2025-10-10 Readme and License added
2025-10-11 Added folder for feature electronics
2025-10-11 Added IO sockets. Diference from usual female pin header is that on silkscreen layer marked placer for plugs
2025-10-11 Added IO pin header connection for IO boards. Removed holes for compatability.
2025-10-11 Readme enhanced
2025-10-12 Added symbols: connectors and sockets that are linked to corresponding footprints.
2025-10-12 Added boards outline drawing with dimensions.
2025-10-12 Added 2 out of 6 DCDC converters B2405S-1W and 2W
2025-10-13 Added DCDC modules. That is all for start.
2025-10-16 Changed dimensions of MBs.
2025-10-17 Added DCDC to L2-MB-IOP as an option so it can be used stanalone without L0 and L1.
2025-10-19 Started routing L2-MB pcb.
2025-10-20 Trying to place all jumpers on board.
2025-10-24 Trying to place everithing on board
2025-10-26 Board first version
2025-10-29 Started first DO board
2025-11-02 Created DIO board.
2025-11-02 Created step for KF141.
2025-12-07 Added Analog Output board for DIP components for testing
